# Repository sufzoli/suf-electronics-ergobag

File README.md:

# suf-electronics-ergobag
Blinking signs for Ergobag school bags

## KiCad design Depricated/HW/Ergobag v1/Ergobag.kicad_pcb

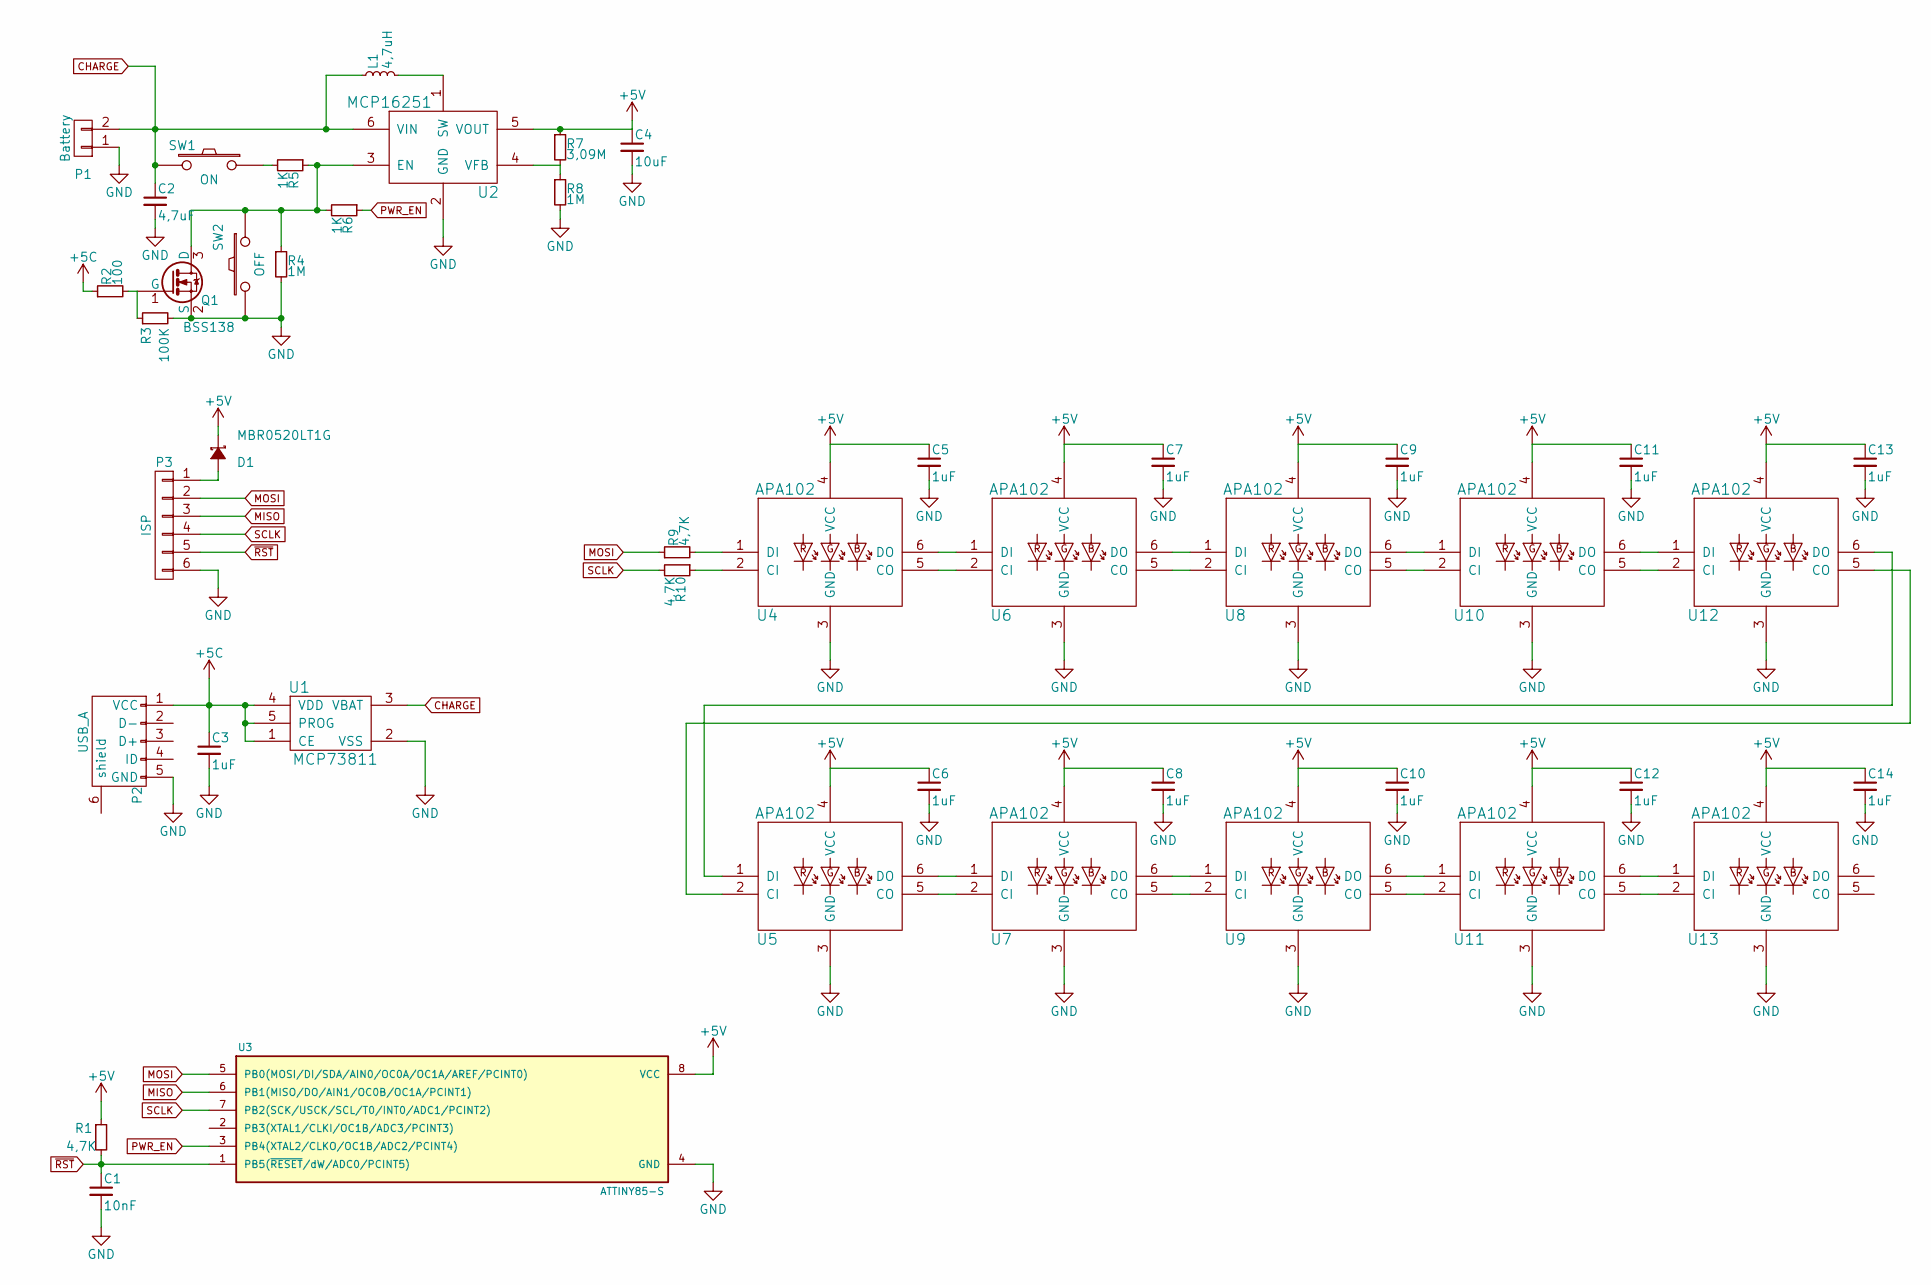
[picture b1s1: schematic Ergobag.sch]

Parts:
C1: 10nF; C_0603_HandSoldering
C2: 4,7uF; C_0603_HandSoldering
C3, C5, C6, C7, C8, C9, C10, C11, C12, C13, C14: 1uF; C_0603_HandSoldering
C4: 10uF; C_0603_HandSoldering
D1: MBR0520LT1G; SOD-123
L1: 4,7uH; R_0805_HandSoldering
P1: Battery; Pin_Header_Angled_1x02
P2: USB_A; USB_Mini-B
P3: ISP; Pin_Header_Straight_1x06
Q1: BSS138; SOT-23_Handsoldering
R1, R9, R10: 4,7K; R_0603_HandSoldering
R2: 100; R_0603_HandSoldering
R3: 100K; R_0603_HandSoldering
R4, R8: 1M; R_0603_HandSoldering
R5, R6: 1K; R_0603_HandSoldering
R7: 3,09M; R_0603_HandSoldering
SW1: ON; SW_Tactile_SPST_Angled
SW2: OFF; SW_Tactile_SPST_Angled
U1: MCP73811; SOT-23-5_Handsoldering
U2: MCP16251; SOT-23-6
U3: ATTINY85-S; SOIJ-8_5.3x5.3mm_Pitch1.27mm
U4, U5, U6, U7, U8, U9, U10, U11, U12, U13: APA102; LED_WS2812-PLCC6

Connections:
+5C: C3.1, P2.1 (VCC), R2.1, U1.1 (CE), U1.4 (VDD), U1.5 (PROG)
+5V: C4.1, C5.1, C6.1, C7.1, C8.1, C9.1, C10.1, C11.1, C12.1, C13.1, C14.1, D1.1 (K), R1.1, R7.1, U2.5 (VOUT), U3.8 (VCC), U4.4 (VCC), U5.4 (VCC), U6.4 (VCC), U7.4 (VCC), U8.4 (VCC), U9.4 (VCC), U10.4 (VCC), U11.4 (VCC), U12.4 (VCC), U13.4 (VCC)
CHARGE: C2.1, L1.1, P1.2, SW1.2, U1.3 (VBAT), U2.6 (VIN)
GND: C1.2, C2.2, C3.2, C4.2, C5.2, C6.2, C7.2, C8.2, C9.2, C10.2, C11.2, C12.2, C13.2, C14.2, P1.1, P2.5 (GND), P3.6, Q1.2 (S), R3.2, R4.2, R8.2, SW2.2, U1.2 (VSS), U2.2 (GND), U3.4 (GND), U4.3 (GND), U5.3 (GND), U6.3 (GND), U7.3 (GND), U8.3 (GND), U9.3 (GND), U10.3 (GND), U11.3 (GND), U12.3 (GND), U13.3 (GND)
MISO: P3.3, U3.6 (PB1(MISO/DO/AIN1/OC0B/OC1A/PCINT1))
MOSI: P3.2, R9.1, U3.5 (PB0(MOSI/DI/SDA/AIN0/OC0A/OC1A/AREF/PCI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)
unnamed: D1.2 (A), P3.1
unnamed: L1.2, U2.1 (SW)
unnamed: Q1.1 (G), R2.2, R3.1
unnamed: Q1.3 (D), R4.1, R5.1, R6.2, SW2.1, U2.3 (EN)
unnamed: R5.2, SW1.1
unnamed: R7.2, R8.1, U2.4 (VFB)
unnamed: R9.2, U4.1 (DI)
unnamed: R10.1, U4.2 (CI)
unnamed: U4.5 (CO), U6.2 (CI)
unnamed: U4.6 (DO), U6.1 (DI)
unnamed: U5.5 (CO), U7.2 (CI)
unnamed: U5.6 (DO), U7.1 (DI)
unnamed: U6.5 (CO), U8.2 (CI)
unnamed: U6.6 (DO), U8.1 (DI)
unnamed: U7.5 (CO), U9.2 (CI)
unnamed: U7.6 (DO), U9.1 (DI)
unnamed: U8.6 (DO), U10.1 (DI)
unnamed: U8.5 (CO), U10.2 (CI)
unnamed: U10.5 (CO), U12.2 (CI)
unnamed: U10.6 (DO), U12.1 (DI)
unnamed: U9.6 (DO), U11.1 (DI)
unnamed: U9.5 (CO), U11.2 (CI)
unnamed: U11.5 (CO), U13.2 (CI)
unnamed: U11.6 (DO), U13.1 (DI)
unnamed: U5.2 (CI), U12.5 (CO)
unnamed: U5.1 (DI), U12.6 (DO)
PWR_EN: R6.1, U3.3 (PB4(XTAL2/CLKO/OC1B/ADC2/PCINT4))
SCLK: P3.4, R10.2, U3.7 (PB2(SCK/USCK/SCL/T0/INT0/ADC1/PCINT2))
~RST: C1.1, P3.5, R1.2, U3.1 (PB5(~RESET~/dW/ADC0/PCINT5))

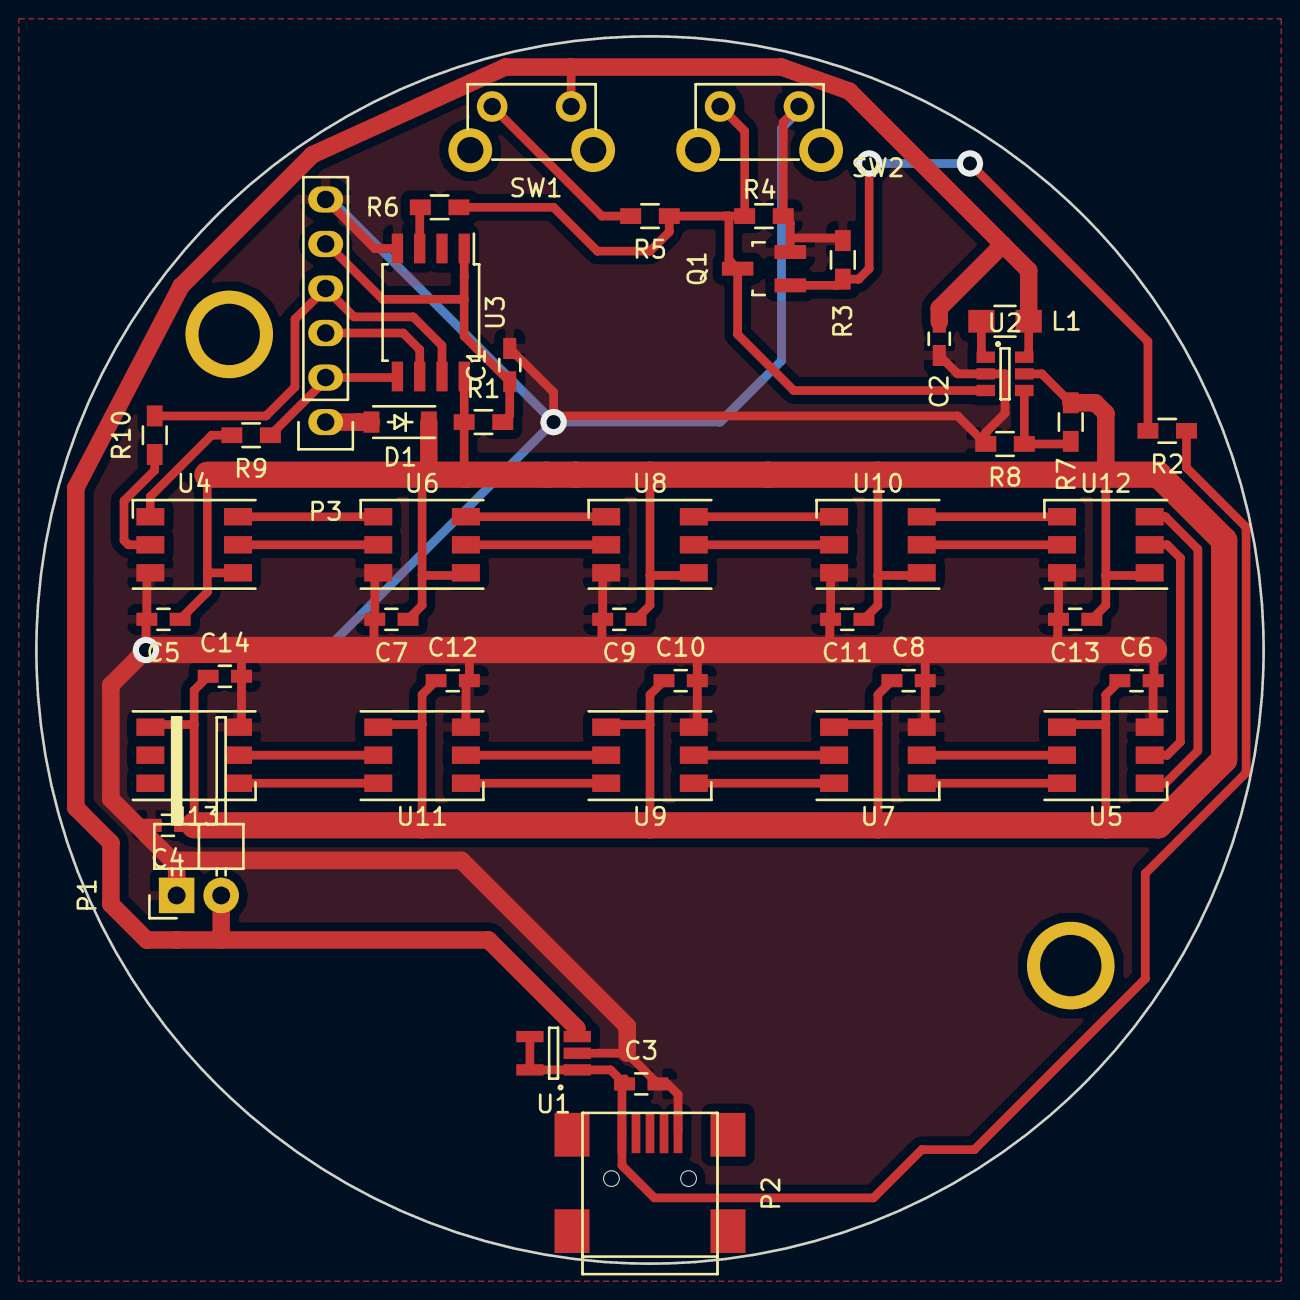
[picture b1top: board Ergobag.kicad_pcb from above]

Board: 2 copper layers, 70.0 x 70.0 mm, 47 parts (0 on the bottom side), 35 nets.

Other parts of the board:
MNT_HOLE_3.5S, MNT_HOLE_3.5S#2: Val**; MNT_HOLE_3.5S

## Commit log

2021-03-20 Add 3D design and deprecated things
